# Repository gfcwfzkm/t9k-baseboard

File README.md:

# t9k-baseboard
Tang Nano 9k Baseboard for Tang Nano 9k FPGA Board.

## Introduction

The main idea is to have a baseboard for the Tang Nano 9k FPGA Board that allows to use it in a more comfortable way.
The baseboard will feature four PMOD connectors, a rotary encoder, a navigation switch and a WS2813-Style 8mm RGB LED.

*A small FPGA dev environment for ~30 CHF!*

The target goal of this project is to give students and hobbyists a platform to learn and experiment with FPGA technology in a more comfortable and cheap way. This project received generous support from the [Bern University of Applied Sciences (BFH)](https://www.bfh.ch/ti/en/). Thank you!

With cost being a main target, the Sipeed Tang Nano 9k FPGA Board was chosen as the base for this project. The board is available for around 14$ and features a Gowin GW1NR-9C with 8640 LUT4. The board is also equipped with a 32Mbit SPI Flash, a 27 MHz clock and a USB-C connector for programming and power.

The baseboard has been designed to be used with either a vanilla Tang Nano 9k Board, or one with the 1.13" SPI Display attached.
While the bigger, parallel RGB displays can still be used, the user will have a lot less PMODs available without conflicts to the display.

## Files
In the `kicad` folder, you will find the KiCad project files for the baseboard.
The project has been designed using KiCad 8.

In the `docs` folder, you will find the [BOM](docs/BOM.pdf) of this project for 10 PCBs, a [PDF schematic](docs/SCHEMA.pdf) of the board and a [Pinmap Table](docs/Pinmap.pdf) to help you assign the various I/Os in code.

Check out the `examples` folder for some example projects to get you started. You can find an [overview of the examples](examples/README.md) there to get started.

## Getting Started
If you haven't gotten the board and the components yet, check out the [BOM](docs/BOM.pdf) to see what you need.

The board has been designed to be hand-assembled, so all you need is a fine soldering iron, tweezers and some solder.

On the software side, you can either use the open source YOSYS toolchain or the official Gowin tools. The board has been tested with the Gowin tools, so you might want to start with those. I recommend getting the full Gowin EDA (not the Educational one) and either request a free license or use Sipeed's license server. Sipeed has an guide on how to setup the IDE [here](https://wiki.sipeed.com/hardware/en/tang/Tang-Nano-Doc/install-the-ide.html).

## Starting a new project on Gowin EDA
This section will guide you through the process of starting a new project on the Gowin EDA.
- Start `GOWIN FPGA Designer` and start a new project by clicking on `File -> New -> New Project...` or by simply clicking `New Project` on the Quick Start page.

- Use a project name of your choice and select the path where you want to store the project. Click `Next`.

- When the `Select Device` window pops up, ensure that the final part number is `GW1NR-LV9QN88PC6/I5` and click `Next`

- The project is now created and you can start adding files to it. To add or create files, right-click on the project in the `Design` tab and select `New File...`

- You can now add a new Verilog or VHDL file to the project. This guide will use VHDL. Name the file `top` (, change the file ending to .vhdl) and click `OK`.

- Paste in the following code - a simple counter that will use the six LEDs on the Tang Nano 9k board
```vhdl
library IEEE;
use IEEE.std_logic_1164.all;
use IEEE.numeric_std.all;
use ieee.math_real.all;

entity top is 
    port (
        clk   : in std_logic;    --! Clock input @ 27 MHz
        rst_n : in std_logic;    --! Active low reset

        leds  : out std_logic_vector(5 downto 0)    --! Output port for the LEDs
    );
end top;

architecture RTL of top is
    -- Increase counter_reg every 6_750_000 clock cycles
    constant CLK_DIV_CNT : positive := 6_750_000;
    -- Width of the CLK_DIV_CNT constant
    constant count_width : integer := integer(ceil(log2(real(CLK_DIV_CNT))));
    
    signal counter_reg : unsigned(5 downto 0)                := (others => '0');
    signal clkdiv_reg  : unsigned(count_width-1 downto 0)    := (others => '0');
begin
    -- Assign the counter value to the LEDs
    leds <= std_logic_vector(counter_reg);
    
    -- Counter and clock divider
    COUNTER : process (clk, rst_n) begin
        if rst_n = '0' then
            -- Reset the counter and clock divider
            counter_reg <= (others => '0');
            clkdiv_reg <= (others => '0');
        elsif rising_edge(clk) then
            -- Increment the clock divider
            clkdiv_reg <= clkdiv_reg + 1;

            -- Check if the clock divider has reached the desired value
            if clkdiv_reg = to_unsigned(CLK_DIV_CNT, count_width) then
                -- Reset the clock divider and increment the counter
                clkdiv_reg <= (others => '0');
                counter_reg <= counter_reg + 1;
            end if;
        end if;
    end process COUNTER;
end architecture RTL;
```

- Before the code can be synthesized, the VHDL standard needs to be set to 2008. This is because the math_real library isn't compiled on Gowin EDA for VHDL-1993. To do this, click on `Project -> Configuration` and select `Synthesize -> General`. Set the `VHDL Language` to `VHDL 2008` and click `OK`

- Now you can synthesize the code by clicking on the top tool bar on `Synthesize` or by double-clicking `Synthesize` in the `Process` tab

- **Nice to know:** You can double-click in the `Process` tab the `Synthesis Report` to see the synthesis results and resource usage of the design. In the menu bar `Tools -> Schematic Viewer -> Design Viewer` you can see the schematic of the design, if you are interested in that.

- Before `Place & Route` can be done, the pinout of the design needs to be set. To do this, click on `Tools -> Floor Planner` menu item. The tool will warn you that no Constraint File is in the project - click `OK` to create one.

- In the `Floor Planner` window, click on the `Package View` tab to get a overview of the FPGA's pins. To assign the various signals in the VHDL file to the pins, open the `I/O Contraints` tab at the bottom of the window

- Using the [Pinmap Table](docs/Pinmap.pdf) in the `docs` folder, assign the signals to the pins by either typing the location / pin number or by drag-n-dropping the signals to the pins in the `Package View`. Also pay attention to the voltage level of the signals. The Pinmap Table will tell you if a signal is 3.3V or 1.8V, so you have to set the `IO Type` to either `LVCMOS33` or `LVCMOS18` respectively. As for the `rst_n` signal, this guide will use the on-board button `S1`

- After all the I/Os have been assigned to a location, click on `File -> Save` to save the constraints file. You can now close the `Floor Planner` window

- Now you can do the `Place & Route` by clicking on the top tool bar on `Place & Route` or by double-clicking `Place & Route` in the `Process` tab

- After the `Place & Route` process has finished, you can download / program the design to the FPGA by clicking on the top tool bar on `Program` or by double-clicking `Program Device` in the `Process` tab

- The `Gowin Programmer` window will open. Click on `USB Cable Settings`, hit `Query/Detect Cable` and click `Save`

- You can now click on `Program` (The play-style button) to program the design to the FPGA. The LEDs on the Tang Nano 9k board should now count up and pressing S1 should reset it

Congratulations! You have now successfully created a simple design for the Tang Nano 9k FPGA Board using the Gowin EDA. You can find the this project and more in the `examples` folder.

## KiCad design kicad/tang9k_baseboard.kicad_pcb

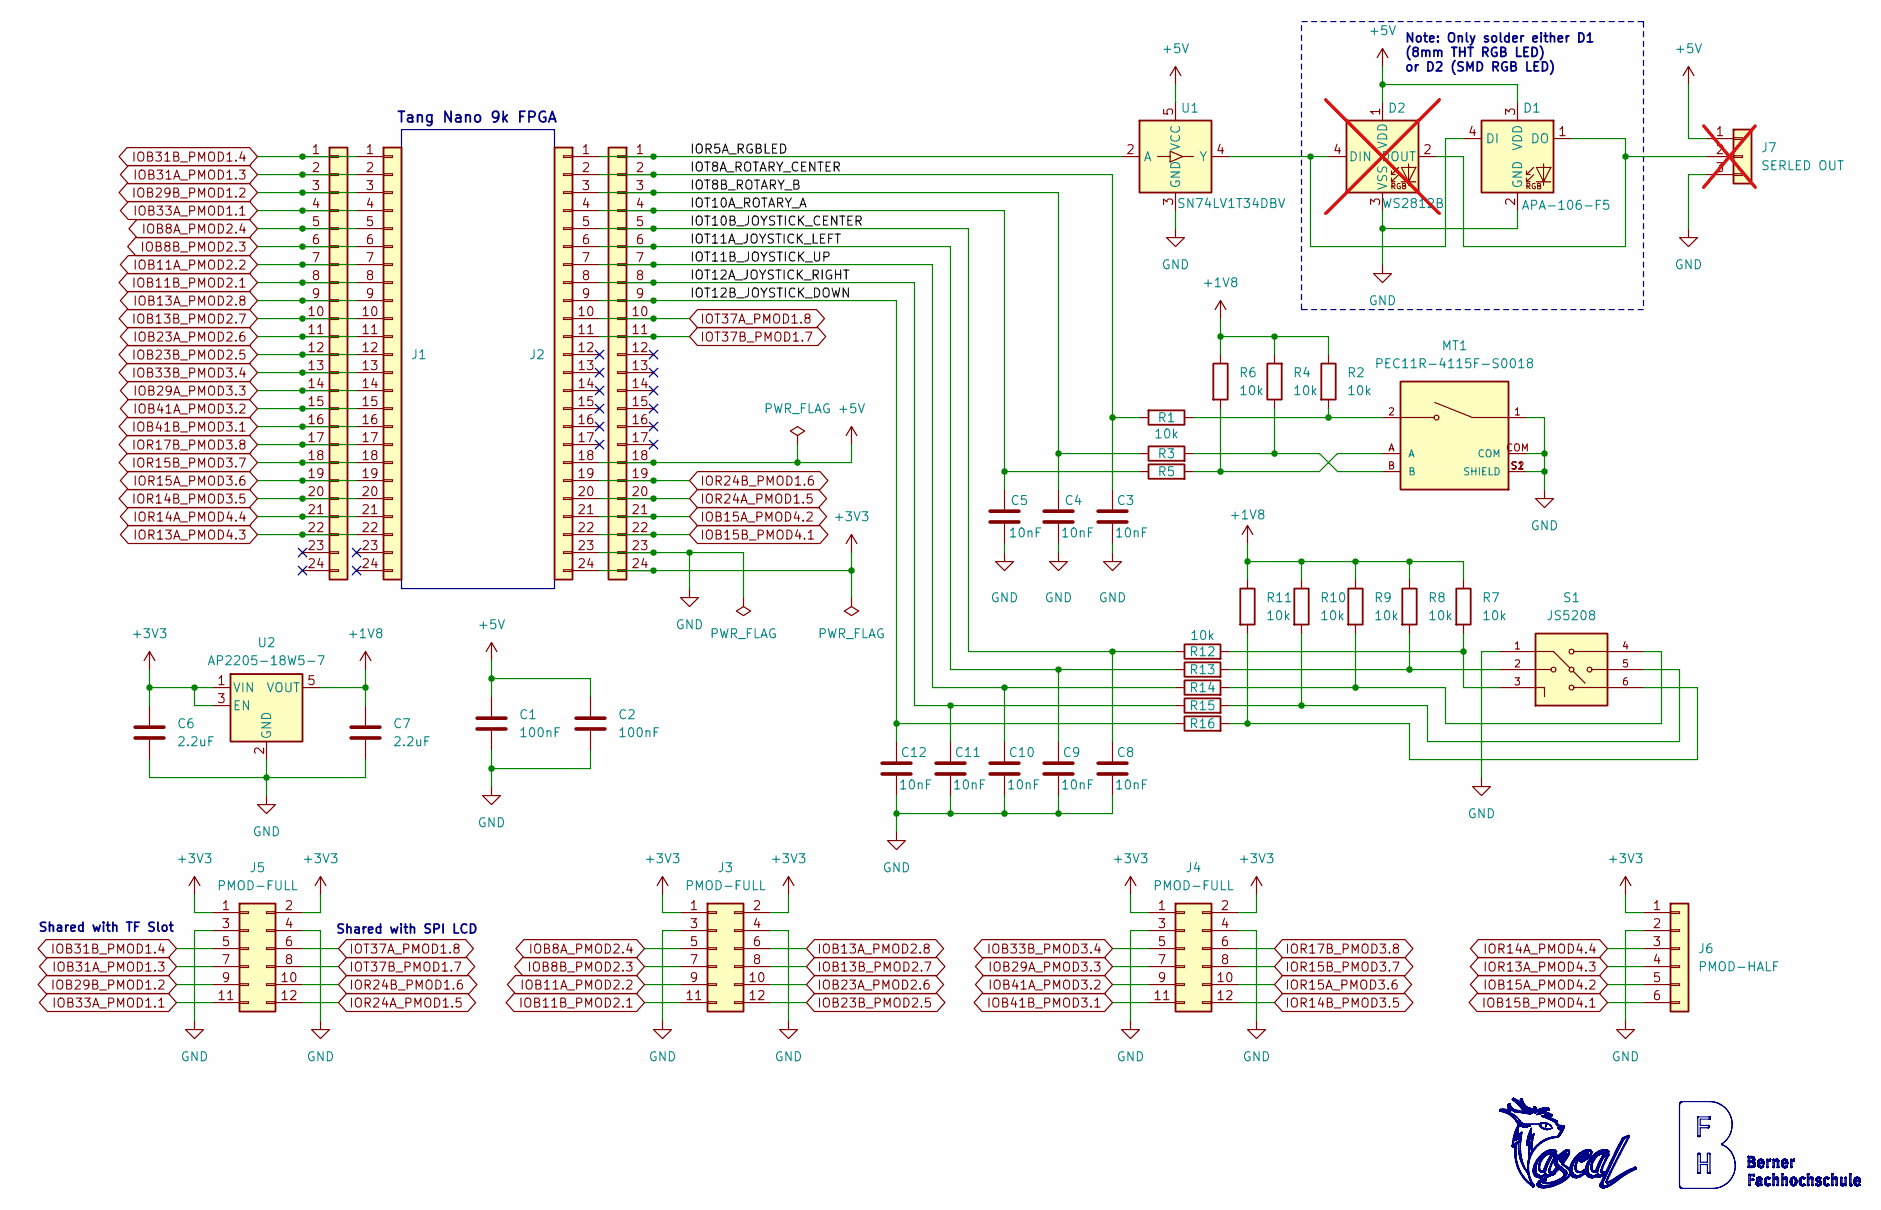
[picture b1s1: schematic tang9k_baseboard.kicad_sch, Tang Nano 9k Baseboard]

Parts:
C1, C2: 100nF; C_0805_2012Metric_Pad1.18x1.45mm_HandSolder; DigiKey_Part_Number 311-1140-1-ND
C3, C4, C5, C8, C9, C10, C11, C12: 10nF; C_0805_2012Metric_Pad1.18x1.45mm_HandSolder; DigiKey_Part_Number 311-1136-1-ND
C6, C7: 2.2uF; C_0805_2012Metric_Pad1.18x1.45mm_HandSolder; DigiKey_Part_Number 4713-GMC21X7R225K25NTCT-ND
D1: APA-106-F5; LED_D5.0mm-4_RGB; DigiKey_Part_Number 1568-1202-ND
D2: WS2812B; LED_WS2812B_PLCC4_5.0x5.0mm_P3.2mm; DigiKey_Part_Number 1568-COM-16347CT-ND; not fitted
J1, J2, J8, J9: FPGA I/O; PinSocket_1x24_P2.54mm_Vertical; DigiKey_Part_Number S7057-ND
J3, J4, J5: PMOD-FULL; PinSocket_2x06_P2.54mm_Horizontal; DigiKey_Part_Number 732-613012243121-ND
J6: PMOD-HALF; PinSocket_1x06_P2.54mm_Horizontal; DigiKey_Part_Number 732-613006143121-ND
J7: SERLED OUT; PinHeader_1x03_P2.54mm_Vertical; not fitted
MT1: PEC11R-4115F-S0018; XDCR_PEC11R-4215F-S0024; PARTREV Rev. 09/19; DigiKey_Part_Number PEC11R-4115F-S0018-ND
R1, R2, R3, R4, R5, R6, R7, R8, R9, R10, R11, R12, R13, R14, R15, R16: 10k; R_0805_2012Metric_Pad1.20x1.40mm_HandSolder; DigiKey_Part_Number 311-10.0KCRCT-ND
S1: JS5208; SW_JS5208; PARTREV D; DigiKey_Part_Number EG4561-ND
U1: SN74LV1T34DBV; SOT-23-5; DigiKey_Part_Number 296-37176-1-ND
U2: AP2205-18W5-7; SOT-23-5; DigiKey_Part_Number 31-AP2205-18W5-7CT-ND

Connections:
+1V8: C7.1, R2.1, R4.2, R6.1, R7.1, R8.1, R9.1, R10.1, R11.1, U2.5 (VOUT)
+3V3: C6.1, J2.24, J3.1, J3.2, J4.1, J4.2, J5.1, J5.2, J6.1, J9.24, U2.1 (VIN), U2.3 (EN)
+5V: C1.1, C2.1, D1.3 (VDD), D2.1 (VDD), J2.18, J7.1, J9.18, U1.5 (VCC)
/IOR5A_RGBLED: J2.1, J9.1, U1.2 (A)
/IOT8A_ROTARY_CENTER: C3.1, J2.2, J9.2, R1.2
/IOT8B_ROTARY_B: C4.1, J2.3, J9.3, R3.1
/IOT10A_ROTARY_A: C5.1, J2.4, J9.4, R5.1
/IOT10B_JOYSTICK_CENTER: C8.1, J2.5, J9.5, R12.1
/IOT11A_JOYSTICK_LEFT: C9.1, J2.6, J9.6, R13.1
/IOT11B_JOYSTICK_UP: C10.1, J2.7, J9.7, R14.1
/IOT12A_JOYSTICK_RIGHT: C11.1, J2.8, J9.8, R15.1
/IOT12B_JOYSTICK_DOWN: C12.1, J2.9, J9.9, R16.1
IOB8A_PMOD2.4: J1.5, J3.5, J8.5
IOB8B_PMOD2.3: J1.6, J3.7, J8.6
IOB11A_PMOD2.2: J1.7, J3.9, J8.7
IOB11B_PMOD2.1: J1.8, J3.11, J8.8
IOB13A_PMOD2.8: J1.9, J3.6, J8.9
IOB13B_PMOD2.7: J1.10, J3.8, J8.10
IOB15A_PMOD4.2: J2.21, J6.5, J9.21
IOB15B_PMOD4.1: J2.22, J6.6, J9.22
IOB23A_PMOD2.6: J1.11, J3.10, J8.11
IOB23B_PMOD2.5: J1.12, J3.12, J8.12
IOB29A_PMOD3.3: J1.14, J4.7, J8.14
IOB29B_PMOD1.2: J1.3, J5.9, J8.3
IOB31A_PMOD1.3: J1.2, J5.7, J8.2
IOB31B_PMOD1.4: J1.1, J5.5, J8.1
IOB33A_PMOD1.1: J1.4, J5.11, J8.4
IOB33B_PMOD3.4: J1.13, J4.5, J8.13
IOB41A_PMOD3.2: J1.15, J4.9, J8.15
IOB41B_PMOD3.1: J1.16, J4.11, J8.16
IOR13A_PMOD4.3: J1.22, J6.4, J8.22
IOR14A_PMOD4.4: J1.21, J6.3, J8.21
IOR14B_PMOD3.5: J1.20, J4.12, J8.20
IOR15A_PMOD3.6: J1.19, J4.10, J8.19
IOR15B_PMOD3.7: J1.18, J4.8, J8.18
IOR17B_PMOD3.8: J1.17, J4.6, J8.17
IOR24A_PMOD1.5: J2.20, J5.12, J9.20
IOR24B_PMOD1.6: J2.19, J5.10, J9.19
IOT37A_PMOD1.8: J2.10, J5.6, J9.10
IOT37B_PMOD1.7: J2.11, J5.8, J9.11
unnamed: D1.4 (DI), D2.4 (DIN), U1.4 (Y)
unnamed: D1.1 (DO), D2.2 (DOUT), J7.2
unnamed: MT1.2, R1.1, R2.2
unnamed: MT1.A, R5.2, R6.2
unnamed: MT1.B, R3.2, R4.1
unnamed: R10.2, R15.2, S1.5
unnamed: R11.2, R16.2, S1.6
unnamed: R8.2, R13.2, S1.2
unnamed: R9.2, R14.2, S1.4

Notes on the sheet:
Tang Nano 9k FPGA
Note: Only solder either D1 (8mm THT RGB LED) or D2 (SMD RGB LED)
Shared with SPI LCD
Shared with TF Slot

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
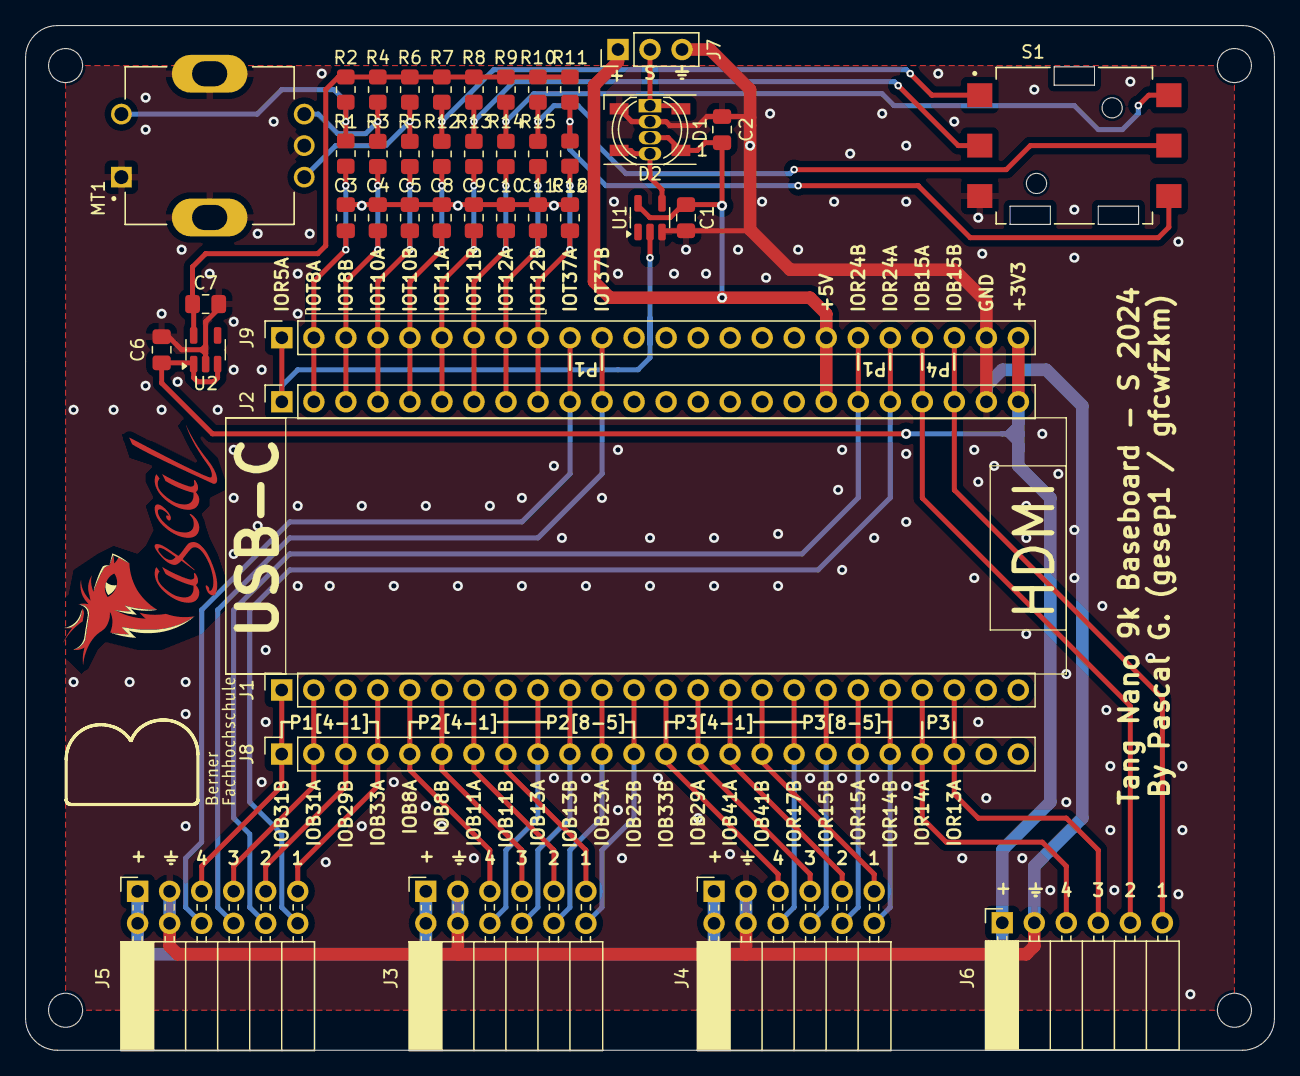
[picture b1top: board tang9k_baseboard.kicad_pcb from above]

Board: 2 copper layers, 99.1 x 81.3 mm, 43 parts (0 on the bottom side), 51 nets.

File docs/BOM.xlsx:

Note: This BOM sheet summarizes the costs for a small production run of 10 piec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
Reference | Value | Footprint | Qty | DNP | DigiKey_Part_Number | Price 10 PCS
C1,C2 | 100nF | Capacitor_SMD:C_0805_2012Metric_Pad1.18x1.45mm_HandSolder | 2 |  | 311-1140-1-ND | 1.28 |  | +1 for everyone
C3,C4,C5,C8,C9,C10,C11,C12 | 10nF | Capacitor_SMD:C_0805_2012Metric_Pad1.18x1.45mm_HandSolder | 8 |  | 311-1136-1-ND | 2.4319999999999999 |  | +1 for everyone
C6,C7 | 2.2uF | Capacitor_SMD:C_0805_2012Metric_Pad1.18x1.45mm_HandSolder | 2 |  | 4713-GMC21X7R225K25NTCT-ND | 1.1600000000000001 |  | +1 for everyone
D1 | APA-106-F5 | LED_THT:LED_D5.0mm-4_RGB | 1 |  | 1568-1202-ND | 12.76
J1,J2,J8,J9 | FPGA I/O | Connector_PinSocket_2.54mm:PinSocket_1x24_P2.54mm_Vertical | 4 |  | S7057-ND | 45.679999999999993
J3,J4,J5 | PMOD-FULL | Connector_PinSocket_2.54mm:PinSocket_2x06_P2.54mm_Horizontal | 3 |  | 732-613012243121-ND | 23.856000000000002
J6 | PMOD-HALF | Connector_PinSocket_2.54mm:PinSocket_1x06_P2.54mm_Horizontal | 1 |  | 732-613006143121-ND | 4.9000000000000004
MT1 | PEC11R-4115F-S0018 | PEC11R-4215F-S0024:XDCR_PEC11R-4215F-S0024 | 1 |  | PEC11R-4115F-S0018-ND | 11.459999999999999
R1,R2,R3,R4,R5,R6,R7,R8,R9,R10,R11,R12,R13,R14,R15,R16 | 10k | Resistor_SMD:R_0805_2012Metric_Pad1.20x1.40mm_HandSolder | 16 |  | 311-10.0KCRCT-ND | 2.0640000000000001 |  | +2 for everyone
S1 | JS5208 | JS5208:SW_JS5208 | 1 |  | EG4561-ND | 24.51
U1 | SN74LV1T34DBV | Package_TO_SOT_SMD:SOT-23-5 | 1 |  | 296-37176-1-ND | 2.8100000000000005 |  | 2 reserve, in case someone ruins / looses one
U2 | AP2205-18W5-7 | Package_TO_SOT_SMD:SOT-23-5 | 1 |  | 31-AP2205-18W5-7CT-ND | 3.37
 |  |  |  | TOTAL COMPONENTS EXCL. FPGA: |  | 136.28199999999998
PCB costs at JLCPCB (blue, HASL (lead), 2 Layers, 99 x 81 mm, 10 Stück |  |  |  |  |  | 5 |  | ~20 CHF shipping
FPGA Sipeed Tang 9k |  | Base variant |  |  |  | 14.68 | Students would order the FPGA separately as some students want other LCDs to go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
 |  | With 7" LCD |  |  |  | 35.880000000000003
 |  | With 5" LCD |  |  |  | 32.090000000000003
 |  | With 4.3" LCD |  |  |  | 26.34
 |  | With 1.14" LCD |  |  |  | 17.78
 | Project cost per student (Excl. Shipping, with FPGA base variant) |  |  |  |  | 33.308199999999999
 |  |  | An FPGA Development System for around ~30 CHF!

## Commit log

2024-07-01 Initial commit of this project
2024-07-12 Fixed minor silkscreen issues
2024-07-12 images side by side pls
2024-07-12 side by side attempt 2
2024-07-12 Gave up, made custom image
2024-07-12 Linking things more nicely
2024-07-13 Added step-by-step guide, fixed Pinmap error
2024-07-13 Fixing image positions
2024-07-13 Added example project
2024-07-13 Updated silkscreen & 3D renders
2024-07-14 Github hates tabs users, obviously
2024-09-30 Initial push of the RGB LED Driver/Demo
2024-10-18 Added RGB-LED example
2024-10-18 Of course I had a typo in the path
2024-10-27 Create .gitattributes to tweak github linguists statistics
2025-06-15 Added HDMI demo
2025-06-15 Fixed some links and changed formatting.
2025-07-02 Due to githubs issue to render tabs at a sane size, changed it to spaces.
2025-07-02 Added docs explaining the RGB-LED example
2025-07-02 Ideas sketching of the chapters
2025-07-04 Enhance README with detailed CPU architecture and instruction set descriptions
2025-07-05 Added documentation for the Fetch and WIP Decode Unit
2025-07-06 Add turing complete solution to the condition level
2025-07-06 Implemented Fetch, Decode and some of the Execute Units
2025-07-07 deleted unwanted simulation dump
2025-07-07 Added more testbenches, converted indentations to spaces
2025-07-07 Simplified testbench
2025-07-07 Implemented additional modules
2025-07-08 Overture Simulation works!
2025-07-08 VHDL file documentations and indentation cleanup
2025-07-09 Added script to run all testbenches
2025-07-10 Turning the toy CPU into a small SoC
2025-07-11 Testbenches for the peripherals
2025-07-14 Overture CPU finished
2025-07-14 Little fixes
2025-07-27 Added FPGA gif
2025-07-27 Moved simple_cpu to seperate repository
2025-07-27 Fixed linking issue
